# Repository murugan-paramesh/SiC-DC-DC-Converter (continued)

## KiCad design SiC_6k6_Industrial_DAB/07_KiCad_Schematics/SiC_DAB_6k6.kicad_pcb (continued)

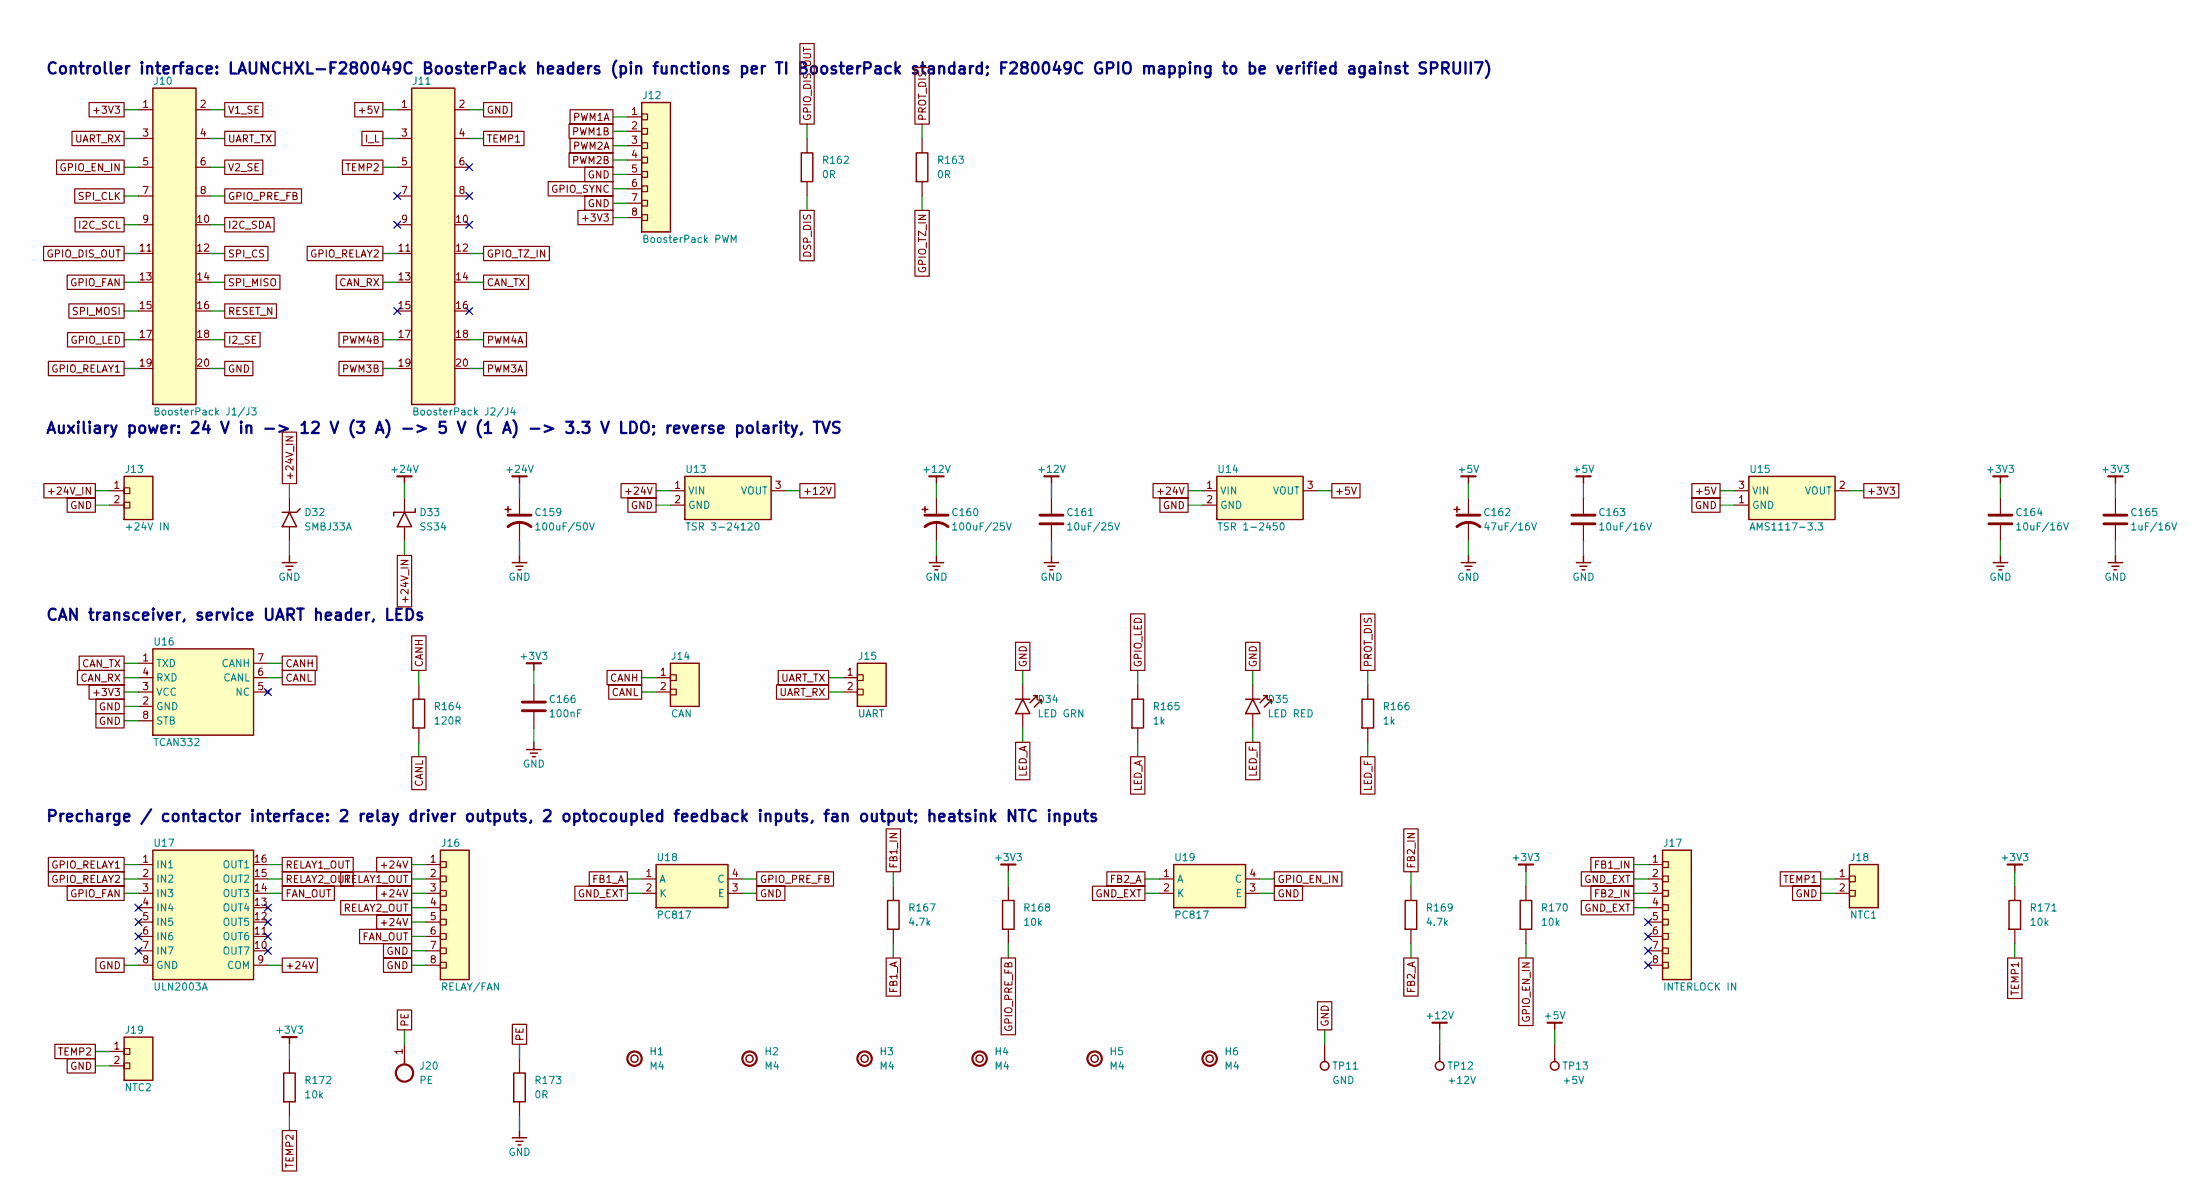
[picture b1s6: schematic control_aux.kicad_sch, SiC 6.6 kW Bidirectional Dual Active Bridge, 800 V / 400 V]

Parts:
C159: 100uF/50V; C_Radial_D8_P3.5
C160: 100uF/25V; C_Radial_D8_P3.5
C161: 10uF/25V; C_1206
C162: 47uF/16V; C_Radial_D8_P3.5
C163, C164: 10uF/16V; C_1206
C165: 1uF/16V; C_0603
C166: 100nF; C_0603
D32: SMBJ33A; D_SMA; MPN Littelfuse SMBJ33A
D33: SS34; D_SMA; MPN Vishay SS34
D34: LED GRN; LED_0805
D35: LED RED; LED_0805
H1, H2, H3, H4, H5, H6: M4; MountingHole_M4
J10: BoosterPack J1/J3; PinHeader_2x10_P2.54; MPN Samtec SSW-110-01-G-D class
J11: BoosterPack J2/J4; PinHeader_2x10_P2.54; MPN Samtec SSW-110-01-G-D class
J12: BoosterPack PWM; PinHeader_1x08_P2.54
J13: +24V IN; TerminalBlock_1x02_P5.08
J14: CAN; TerminalBlock_1x02_P5.08
J15: UART; PinHeader_1x02_P2.54
J16: RELAY/FAN; PinHeader_1x08_P2.54
J17: INTERLOCK IN; PinHeader_1x08_P2.54
J18: NTC1; PinHeader_1x02_P2.54
J19: NTC2; PinHeader_1x02_P2.54
J20: PE; Lug_M5
R162, R163: 0R; R_0603
R164: 120R; R_0603
R165, R166: 1k; R_0603
R167, R169: 4.7k; R_0805
R168, R170, R171, R172: 10k; R_0603
R173: 0R; R_1206
TP11: GND; TestPoint
TP12: +12V; TestPoint
TP13: +5V; TestPoint
U13: TSR 3-24120; SIP-3_TSR; MPN TRACO TSR 3-24120
U14: TSR 1-2450; SIP-3_TSR; MPN TRACO TSR 1-2450
U15: AMS1117-3.3; SOT-223; MPN AMS1117-3.3
U16: TCAN332; SOIC-8; MPN TI TCAN332D
U17: ULN2003A; SOIC-16; MPN TI ULN2003AD
U18, U19: PC817; DIP-4; MPN Sharp PC817

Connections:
+3V3: C164.1, C165.1, C166.1, J10.1, J12.8, R168.1, R170.1, R171.1, R172.1, U15.2 (VOUT), U16.3 (VCC); also elsewhere on the board
+5V: C162.1 (+), C163.1, J11.1, TP13.1, U14.3 (VOUT), U15.3 (VIN); also elsewhere on the board
+12V: C160.1 (+), C161.1, TP12.1, U13.3 (VOUT); also elsewhere on the board
+24V: C159.1 (+), D33.1 (K), J16.1, J16.3, J16.5, U13.1 (VIN), U14.1 (VIN), U17.9 (COM)
+24V_IN: D32.1 (K), D33.2 (A), J13.1
CANH: J14.1, R164.1, U16.7 (CANH)
CANL: J14.2, R164.2, U16.6 (CANL)
CAN_RX: J11.13, U16.4 (RXD)
CAN_TX: J11.14, U16.1 (TXD)
DSP_DIS: R162.2; also elsewhere on the board
FAN_OUT: J16.6, U17.14 (OUT3)
FB1_A: R167.2, U18.1 (A)
FB1_IN: J17.1, R167.1
FB2_A: R169.2, U19.1 (A)
FB2_IN: J17.3, R169.1
GND: C159.2 (-), C160.2 (-), C161.2, C162.2 (-), C163.2, C164.2, C165.2, C166.2, D32.2 (A), D34.1 (K), D35.1 (K), J10.20, J11.2, J12.5, J12.7, J13.2, J16.7, J16.8, J18.2, J19.2, R173.2, TP11.1, U13.2 (GND), U14.2 (GND), U15.1 (GND), U16.2 (GND), U16.8 (STB), U17.8 (GND), U18.3 (E), U19.3 (E); also elsewhere on the board
GND_EXT: J17.2, J17.4, U18.2 (K), U19.2 (K)
GPIO_DIS_OUT: J10.11, R162.1
GPIO_EN_IN: J10.5, R170.2, U19.4 (C)
GPIO_FAN: J10.13, U17.3 (IN3)
GPIO_LED: J10.17, R165.1
GPIO_PRE_FB: J10.8, R168.2, U18.4 (C)
GPIO_RELAY1: J10.19, U17.1 (IN1)
GPIO_RELAY2: J11.11, U17.2 (IN2)
GPIO_SYNC: J12.6
GPIO_TZ_IN: J11.12, R163.2
I2C_SCL: J10.9
I2C_SDA: J10.10
I2_SE: J10.18; also elsewhere on the board
I_L: J11.3; also elsewhere on the board
LED_A: D34.2 (A), R165.2
LED_F: D35.2 (A), R166.2
PE: J20.1, R173.1
PROT_DIS: R163.1, R166.1; also elsewhere on the board
PWM1A: J12.1; also elsewhere on the board
PWM1B: J12.2; also elsewhere on the board
PWM2A: J12.3; also elsewhere on the board
PWM2B: J12.4; also elsewhere on the board
PWM3A: J11.20; also elsewhere on the board
PWM3B: J11.19; also elsewhere on the board
PWM4A: J11.18; also elsewhere on the board
PWM4B: J11.17; also elsewhere on the board
RELAY1_OUT: J16.2, U17.16 (OUT1)
RELAY2_OUT: J16.4, U17.15 (OUT2)
RESET_N: J10.16
SPI_CLK: J10.7
SPI_CS: J10.12
SPI_MISO: J10.14
SPI_MOSI: J10.15
TEMP1: J11.4, J18.1, R171.2
TEMP2: J11.5, J19.1, R172.2
UART_RX: J10.3, J15.2
UART_TX: J10.4, J15.1
V1_SE: J10.2; also elsewhere on the board
V2_SE: J10.6; also elsewhere on the board

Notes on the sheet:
Controller interface: LAUNCHXL-F280049C BoosterPack headers (pin functions per TI BoosterPack standard; F280049C GPIO mapping to be verified against SPRUII7)
Auxiliary power: 24 V in -> 12 V (3 A) -> 5 V (1 A) -> 3.3 V LDO; reverse polarity, TVS
CAN transceiver, service UART header, LEDs
Precharge / contactor interface: 2 relay driver outputs, 2 optocoupled feedback inputs, fan output; heatsink NTC inputs

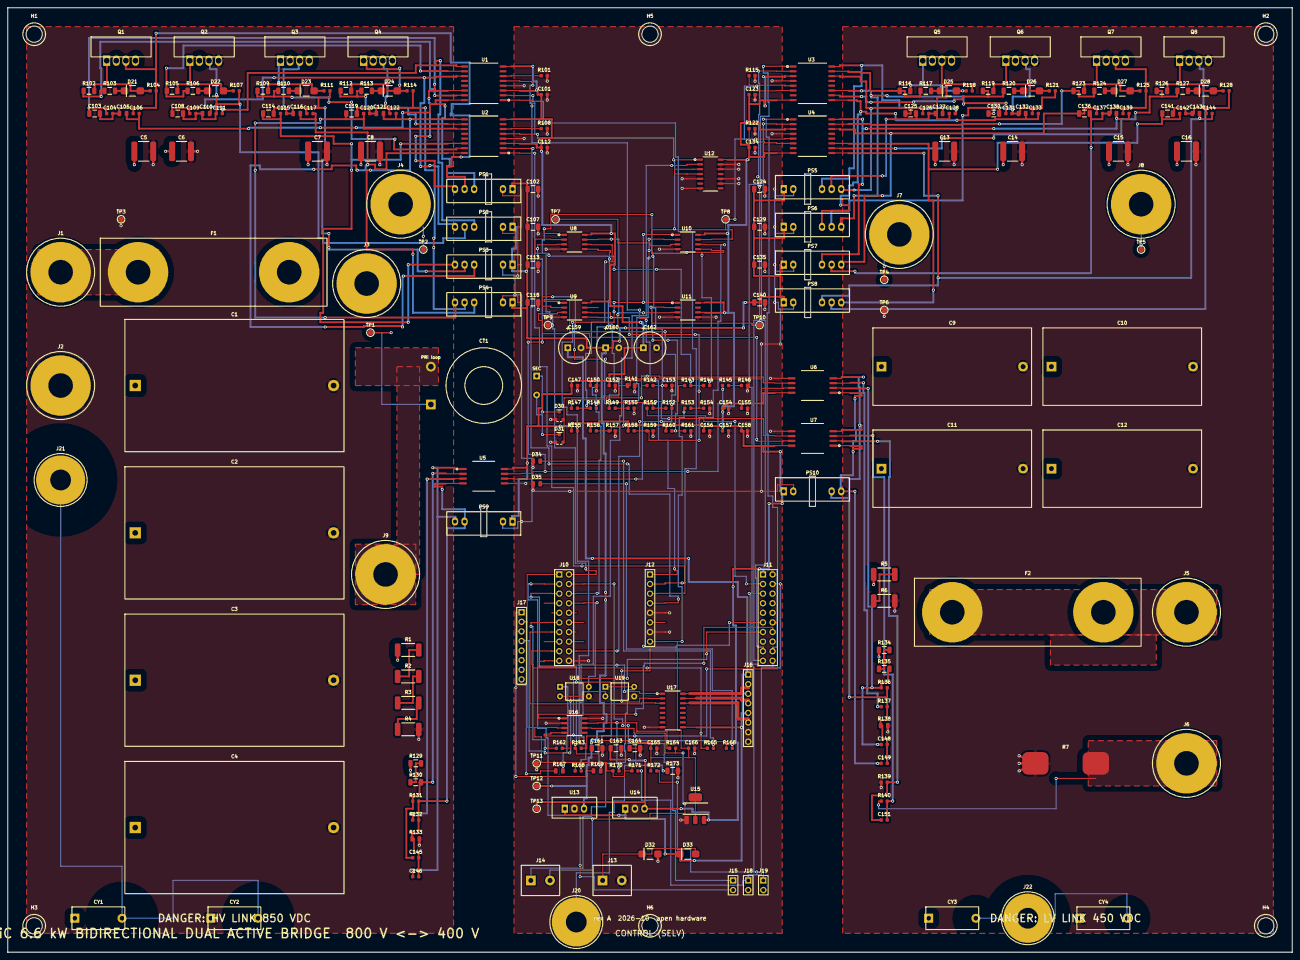
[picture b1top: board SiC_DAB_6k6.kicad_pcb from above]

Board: 6 copper layers, 340.0 x 250.0 mm, 261 parts (0 on the bottom side), 148 nets.

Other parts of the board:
J21: PE_HV; Lug_M5
J22: PE_LV; Lug_M5

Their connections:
PE_HV: J21.1; also elsewhere on the board
PE_LV: J22.1; also elsewhere on the board

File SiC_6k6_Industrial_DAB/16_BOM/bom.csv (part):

qty,refs,value,package,manufacturer,mpn,rating,datasheet,unit_cost,alternatives,procurement,description
4,"C1, C2, C3, C4",20uF/1100V,C_Film_P52.5,TDK,B32778J0206K (verify 1100 V variant),"film, 1100 V DC; used at 850 V (77 %)",https://www.tdk-electronics.tdk.com/,not verified,,PART SELECTION TO VERIFY,HV DC-link film capacitor
5,"C101, C112, C123, C134, C165",1uF/16V,C_0603,,,,,not verified,,PART SELECTION TO VERIFY,U1 VCCI decoupling
17,"C102, C103, C107, C108, C113, C114, C118, C119, C124, C125, C129, C130, C135, C136, C140, C141, C161",10uF/25V,C_1206,,,,,not verified,,PART SELECTION TO VERIFY,PS1 input capacitor
16,"C104, C106, C109, C111, C115, C117, C120, C122, C126, C128, C131, C133, C137, C139, C142, C144",1uF/50V,C_0603,,,,,not verified,,PART SELECTION TO VERIFY,Q1 +15 V HF
8,"C105, C110, C116, C121, C127, C132, C138, C143",4.7uF/25V,C_0805,,,,,not verified,,PART SELECTION TO VERIFY,Q1 -3 V bulk
4,"C13, C14, C15, C16",220nF/630V,C_2220,TDK,CGA9P4X7T2J224K (verify),X7T 630 V MLCC; used at 450 V (71 %),,not verified,,PART SELECTION TO VERIFY,"LV bridge HF decoupling, one pair per leg"
2,"C145, C148",1nF,C_0603,,,,,not verified,,PART SELECTION TO VERIFY,HV sense filter
11,"C146, C147, C149, C150, C152, C154, C155, C156, C157, C158, C166",100nF,C_0603,,,,,not verified,,PART SELECTION TO VERIFY,AMC1301 VDD1 decoupling
1,C151,10nF,C_0603,,,,,not verified,,PART SELECTION TO VERIFY,Shunt sense differential filter
1,C153,220pF,C_0603,,,,,not verified,,PART SELECTION TO VERIFY,I_L filter C0G
1,C159,100uF/50V,C_Radial_D8_P3.5,,,,,not verified,,PART SELECTION TO VERIFY,24 V bulk
1,C160,100uF/25V,C_Radial_D8_P3.5,,,,,not verified,,PART SELECTION TO VERIFY,12 V bulk
1,C162,47uF/16V,C_Radial_D8_P3.5,,,,,not verified,,PART SELECTION TO VERIFY,5 V bulk
2,"C163, C164",10uF/16V,C_1206,,,,,not verified,,PART SELECTION TO VERIFY,5 V HF
4,"C5, C6, C7, C8",100nF/1kV,C_2220,TDK,CGA9N4X7T2W104K (verify),X7T 1 kV MLCC; used at 850 V (85 %) - consider 2 kV part,,not verified,,PART SELECTION TO VERIFY,"HV bridge HF decoupling, one pair per leg"
4,"C9, C10, C11, C12",30uF/700V,C_Film_P37.5,TDK,B32778G7306K (verify),"film, 700 V DC; used at 450 V (64 %)",https://www.tdk-electronics.tdk.com/,not verified,,PART SELECTION TO VERIFY,LV DC-link film capacitor
1,CT1,CT 1:100,CT_Toroid_Straddle,Magnetics,ZW42908TC + 100T AWG32,,,not verified,,,Inductor current CT: one-turn insulated lead from J3 (SW_A) to the external inductor; secondary on the control side
4,"CY1, CY2, CY3, CY4",4.7nF Y1,C_Y1_P12.5,Vishay,VY1472M63Y5UQ63V0,"Y1 safety capacitor, 500 Vac",https://www.vishay.com/,not verified,,,Y1 capacitor HV+ to PE (first CM filter element)
8,"D21, D22, D23, D24, D25, D26, D27, D28",SS14,D_SMA,Vishay,SS14,,,not verified,,,Q1 turn-off steering diode
2,"D30, D31",BAV99,SOT-23,,,,,not verified,,PART SELECTION TO VERIFY,CT bridge rectifier half
1,D32,SMBJ33A,D_SMA,Littelfuse,SMBJ33A,,,not verified,,,24 V input TVS
1,D33,SS34,D_SMA,Vishay,SS34,,,not verified,,,Reverse-polarity series diode
1,D34,LED GRN,LED_0805,,,,,not verified,,PART SELECTION TO VERIFY,Status LED
1,D35,LED RED,LED_0805,,,,,not verified,,PART SELECTION TO VERIFY,Fault LED (PROT_DIS)
1,F1,16A/1000V,Fuse_Terminal_M6,Bussmann,FWP-16A14F class (verify),,,not verified,,PART SELECTION TO VERIFY,HV semiconductor fuse on M6 terminals
1,F2,32A/700V,Fuse_Terminal_M6,Bussmann,FWP-32A14F class (verify),,,not verified,,PART SELECTION TO VERIFY,LV semiconductor fuse on M6 terminals
1,J1,HV+,Stud_M6,,,,,not verified,,PART SELECTION TO VERIFY,HV port + (M6 stud); external semiconductor fuse 16 A/1000 V and precharge contactor in series
1,J10,BoosterPack J1/J3,PinHeader_2x10_P2.54,Samtec,SSW-110-01-G-D class,,,not verified,,PINOUT TO VERIFY ; PART SELECTION TO VERIFY,BoosterPack header 1 (pins 1-20)
1,J11,BoosterPack J2/J4,PinHeader_2x10_P2.54,Samtec,SSW-110-01-G-D class,,,not verified,,PINOUT TO VERIFY ; PART SELECTION TO VERIFY,"BoosterPack header 2 (pins 21-40); PWM1A/B, PWM2A/B on the third header J12"
1,J12,BoosterPack PWM,PinHeader_1x08_P2.54,,,,,not verified,,PINOUT TO VERIFY ; PART SELECTION TO VERIFY,"Additional PWM header (LaunchPad J5/J6 extension), to be mapped"
1,J13,+24V IN,TerminalBlock_1x02_P5.08,,,,,not verified,,PART SELECTION TO VERIFY,24 V auxiliary input
1,J14,CAN,TerminalBlock_1x02_P5.08,,,,,not verified,,PART SELECTION TO VERIFY,CAN bus terminal
1,J15,UART,PinHeader_1x02_P2.54,,,,,not verified,,PART SELECTION TO VERIFY,Service UART (3.3 V)
1,J16,RELAY/FAN,PinHeader_1x08_P2.54,,,,,not verified,,PART SELECTION TO VERIFY,"Contactor coil and fan outputs (24 V, 500 mA max each)"
1,J17,INTERLOCK IN,PinHeader_1x08_P2.54,,,,,not verified,,PART SELECTION TO VERIFY,"Isolated 24 V inputs: precharge feedback, external enable"
1,J18,NTC1,PinHeader_1x02_P2.54,,,,,not verified,,PART SELECTION TO VERIFY,HV heatsink NTC 10k
1,J19,NTC2,PinHeader_1x02_P2.54,,,,,not verified,,PART SELECTION TO VERIFY,LV heatsink NTC 10k
1,J2,HV-,Stud_M6,,,,,not verified,,PART SELECTION TO VERIFY,HV port -
1,J20,PE,Lug_M5,,,,,not verified,,PART SELECTION TO VERIFY,Protective earth stud (bonded to heatsinks and enclosure)
1,J21,PE_HV,Lug_M5,,,,,not verified,,PART SELECTION TO VERIFY,"PE lug of the HV region: Y-capacitor return, bonded to the HV heatsink / enclosure (the three PE lugs are joined through the chassis, not on the PCB, because no copper may cross the isolation barriers)"
1,J22,PE_LV,Lug_M5,,,,,not verified,,PART SELECTION TO VERIFY,"PE lug of the LV region: Y-capacitor return, bonded to the LV heatsink / enclosure"
1,J3,SW_A,Stud_M6,,,,,not verified,,PART SELECTION TO VERIFY,HV bridge output A -> external series inductor L1
1,J4,SW_B,Stud_M6,,,,,not verified,,PART SELECTION TO VERIFY,HV bridge output B -> transformer primary
1,J5,LV+,Stud_M6,,,,,not verified,,PART SELECTION TO VERIFY,LV port + (M6 stud); external fuse/contactor in series
1,J6,LV-,Stud_M6,,,,,not verified,,PART SELECTION TO VERIFY,LV port - (through the current shunt)
1,J7,SW_C,Stud_M6,,,,,not verified,,PART SELECTION TO VERIFY,LV bridge output C -> transformer secondary
1,J8,SW_D,Stud_M6,,,,,not verified,,PART SELECTION TO VERIFY,LV bridge output D -> transformer secondary
1,J9,L1 (via CT),Stud_M6,,,,,not verified,,PART SELECTION TO VERIFY,Stud for the inductor lead after the CT loop
8,"PS1, PS2, PS3, PS4, PS5, PS6, PS7, PS8",R12P21503D,SIP-7_IsoDCDC,RECOM,"R12P21503D (basic-class isolation; reinforced-rated module is an open item, see 15.1)","2 W, 5.2 kVDC isolation (basic class) - open item 15.1",https://recom-power.com/,not verified,,PINOUT TO VERIFY ; PART SELECTION TO VERIFY,Isolated gate bias Q1
1,PS10,ISO 5V/5V 1W SIP-7,SIP-7_IsoDCDC_1W,TBD,- as PS9,"1 W isolated 5 V module, SIP-7 outline, reinforced-rated part to be selected (open item 15.1)",,not verified,,PINOUT TO VERIFY,1 W isolated 5 V for the LV-side sensors
1,PS9,ISO 5V/5V 1W SIP-7,SIP-7_IsoDCDC_1W,TBD,"- 1 W 5 V->5 V isolated module, SIP-7 outline with >= 7.6 mm input/output pin gap, reinforced-rated (a 2.54 mm pitch SIP-4 such as R1SE cannot meet the 5.5 mm module creepage rule)","1 W isolated 5 V module, SIP-7 outline, reinforced-rated part to be selected (open item 15.1)",,not verified,,PINOUT TO VERIFY,1 W isolated 5 V for the HV-side sensor
4,"Q1, Q2, Q3, Q4",C3M0032120K,TO-247-4_Vertical,Wolfspeed,C3M0032120K,"1200 V, 32 mOhm, Tj 175 C; used at 850 V (71 %), Tj < 70 C calc.",https://www.wolfspeed.com/c3m0032120k/,not verified,,,"HV bridge SiC MOSFET 1200 V, high side leg A"
4,"Q5, Q6, Q7, Q8",C3M0016120K,TO-247-4_Vertical,Wolfspeed,C3M0016120K,"1200 V, 16 mOhm; used at 450 V (38 %)",https://www.wolfspeed.com/c3m0016120k/,not verified,,,"LV bridge SiC MOSFET 1200 V, high side leg C"
4,"R1, R2, R3, R4",680k/2W,R_2512,,,"2512, 2 W; 212 V per resistor (voltage rating 500 V)",,not verified,,PART SELECTION TO VERIFY,"HV bleeder chain 2.7 MOhm (4 x 680 k, 850 V / 4 = 212 V per resistor)"
4,"R101, R108, R115, R122",2.2k,R_0603,,,,,not verified,,PART SELECTION TO VERIFY,U1 interlock dead time ~22 ns
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
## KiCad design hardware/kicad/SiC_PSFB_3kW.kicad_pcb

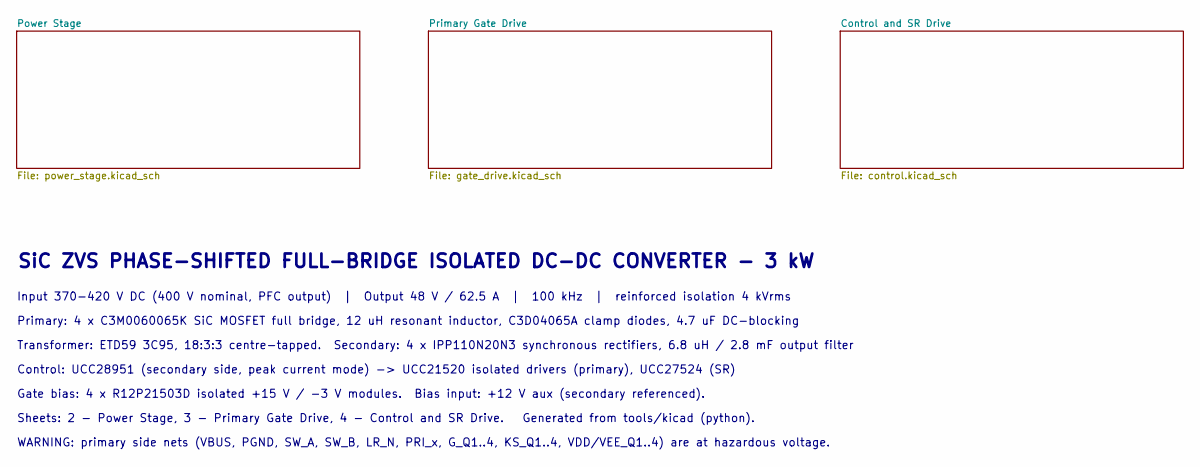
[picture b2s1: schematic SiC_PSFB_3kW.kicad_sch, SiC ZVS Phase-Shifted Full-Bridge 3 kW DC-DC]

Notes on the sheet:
SiC ZVS PHASE-SHIFTED FULL-BRIDGE ISOLATED DC-DC CONVERTER - 3 kW
Input 370-420 V DC (400 V nominal, PFC output) | Output 48 V / 62.5 A | 100 kHz | reinforced isolation 4 kVrms
Primary: 4 x C3M0060065K SiC MOSFET full bridge, 12 uH resonant inductor, C3D04065A clamp diodes, 4.7 uF DC-blocking
Transformer: ETD59 3C95, 18:3:3 centre-tapped. Secondary: 4 x IPP110N20N3 synchronous rectifiers, 6.8 uH / 2.8 mF output filter
Control: UCC28951 (secondary side, peak current mode) -> UCC21520 isolated drivers (primary), UCC27524 (SR)
Gate bias: 4 x R12P21503D isolated +15 V / -3 V modules. Bias input: +12 V aux (secondary referenced).
Sheets: 2 - Power Stage, 3 - Primary Gate Drive, 4 - Control and SR Drive. Generated from tools/kicad (python).
WARNING: primary side nets (VBUS, PGND, SW_A, SW_B, LR_N, PRI_x, G_Q1..4, KS_Q1..4, VDD/VEE_Q1..4) are at hazardous voltage.

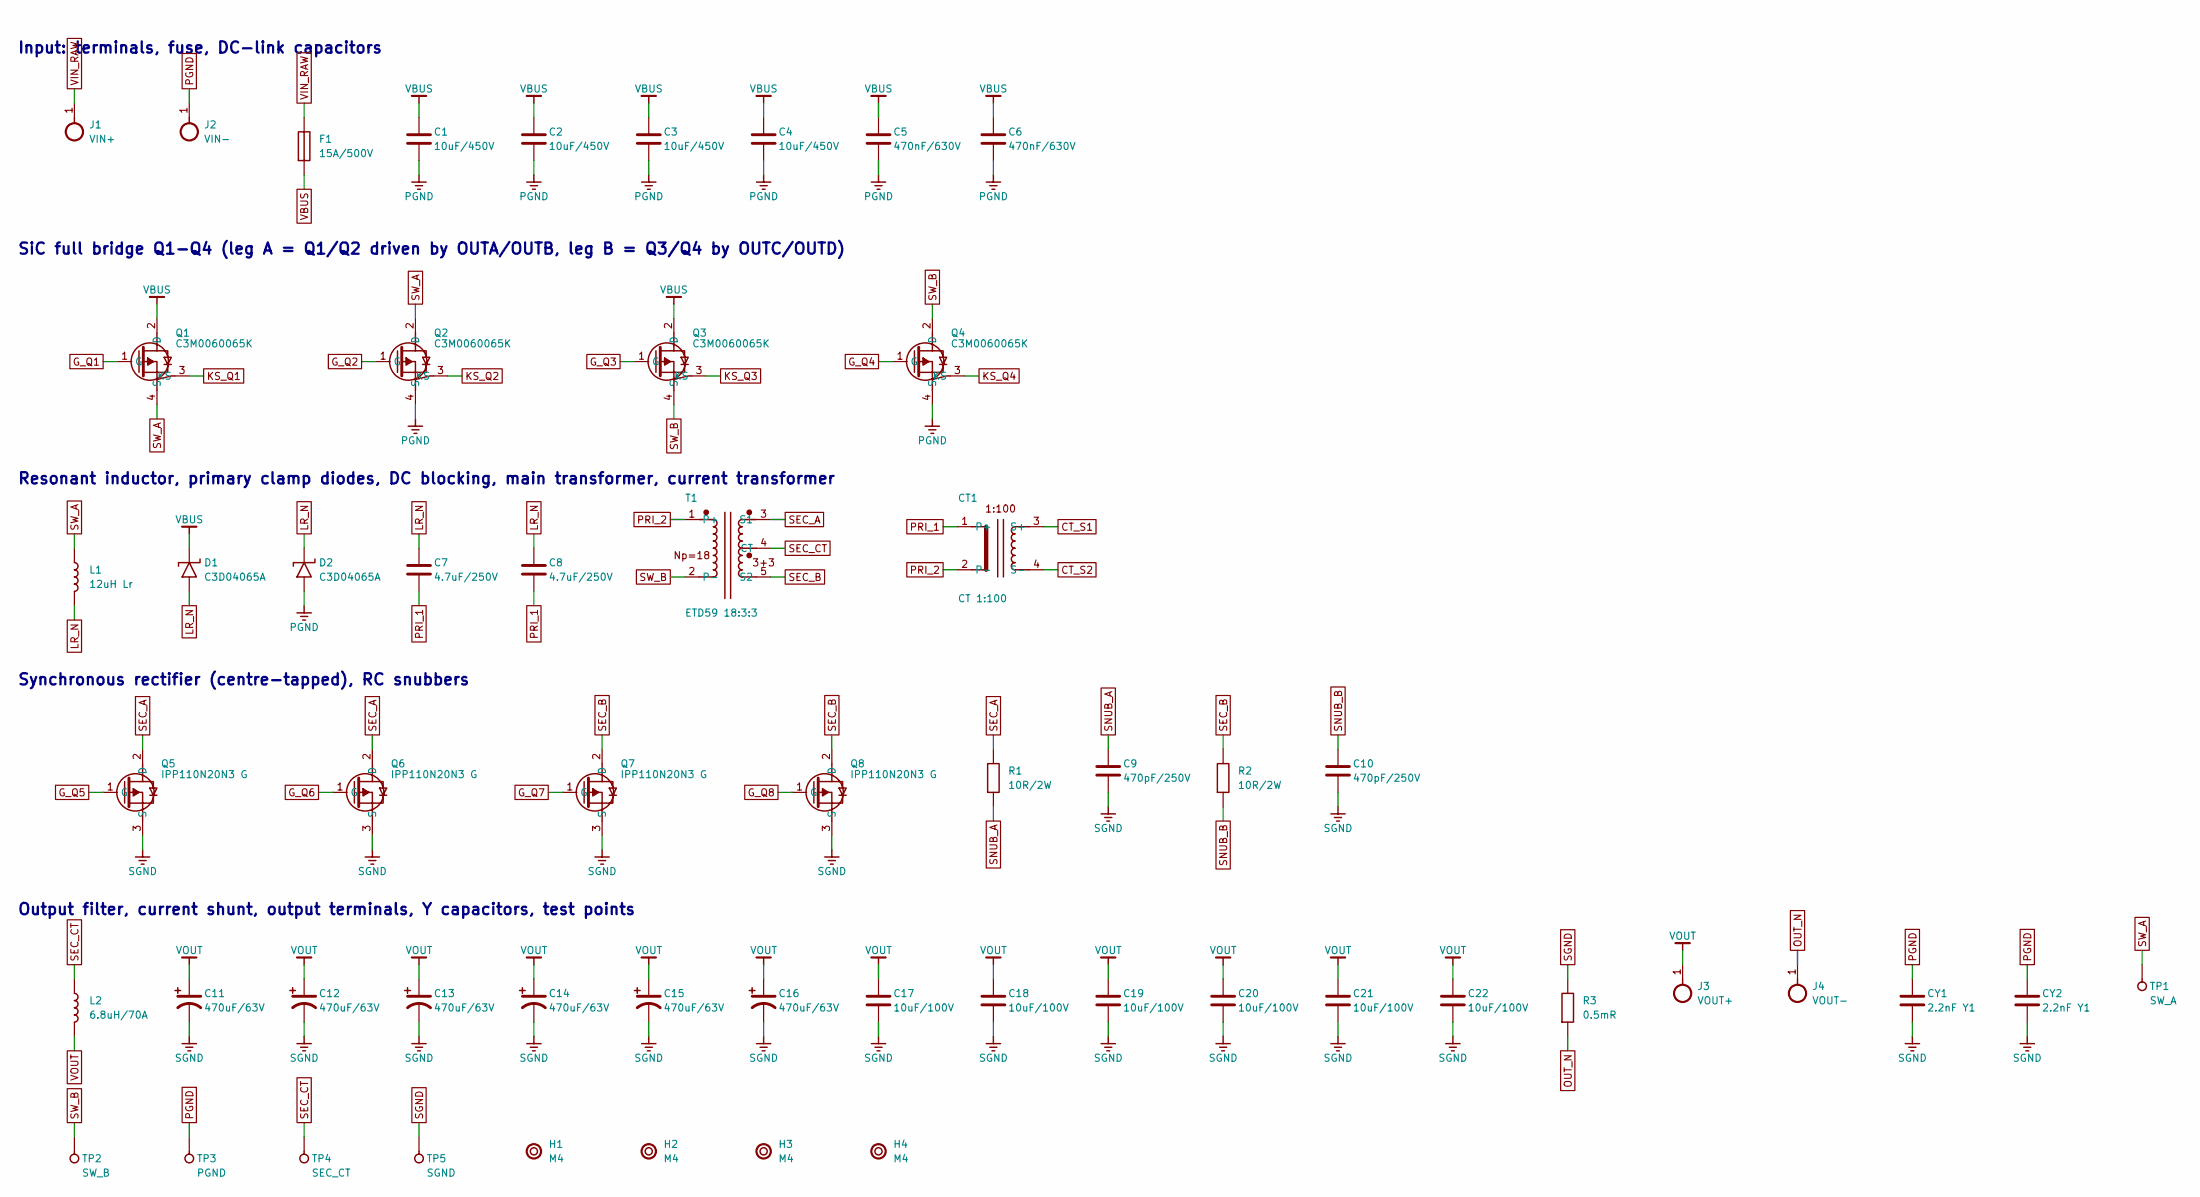
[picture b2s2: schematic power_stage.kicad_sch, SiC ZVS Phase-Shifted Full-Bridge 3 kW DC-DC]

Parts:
C1, C2, C3, C4: 10uF/450V; C_Film_P37.5; MPN TDK B32778G4106K
C5, C6: 470nF/630V; C_2220; MPN TDK CGA9P4X7T2J474K
C7, C8: 4.7uF/250V; C_Film_P22.5; MPN TDK B32674D3475K
C9, C10: 470pF/250V; C_1206
C11, C12, C13, C14, C15, C16: 470uF/63V; C_Radial_D16_P7.5; MPN Nichicon UHW1J471MHD
C17, C18, C19, C20, C21, C22: 10uF/100V; C_1210; MPN TDK CGA6P3X7S2A106K
CT1: CT 1:100; CT_Toroid_Straddle; MPN Magnetics ZW42908TC + 100T AWG32 (or Pu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
CY1, CY2: 2.2nF Y1; C_Y1_P12.5; MPN Vishay VY1222M63Y5UQ63V0
D1, D2: C3D04065A; TO-220-2_Vertical; MPN Wolfspeed C3D04065A
F1: 15A/500V; Fuse_6.3x32_Clips; MPN Littelfuse 0215015.MXP
H1, H2, H3, H4: M4; MountingHole_M4
J1: VIN+; Lug_M4
J2: VIN-; Lug_M4
J3: VOUT+; Lug_M5
J4: VOUT-; Lug_M5
L1: 12uH Lr; Inductor_ETD39_Lr; MPN custom ETD39/3C95 10T litz
L2: 6.8uH/70A; Inductor_Toroid_D52_Lo; MPN custom 2x Magnetics 77439-A7, 5T flat w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
Q1, Q2, Q3, Q4: C3M0060065K; TO-247-4_Vertical; MPN Wolfspeed C3M0060065K
Q5, Q6, Q7, Q8: IPP110N20N3 G; TO-220-3_Vertical; MPN Infineon IPP110N20N3 G
R1, R2: 10R/2W; R_2512
R3: 0.5mR; R_Shunt_8518; MPN Vishay WSBS8518L5000JK
T1: ETD59 18:3:3; Transformer_ETD59_PSFB; MPN custom, see docs/06
TP1: SW_A; TestPoint
TP2: SW_B; TestPoint
TP3: PGND; TestPoint
TP4: SEC_CT; TestPoint
TP5: SGND; TestPoint

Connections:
CT_S1: CT1.3 (S+); also elsewhere on the board
CT_S2: CT1.4 (S-); also elsewhere on the board
G_Q1: Q1.1 (G); also elsewhere on the board
G_Q2: Q2.1 (G); also elsewhere on the board
G_Q3: Q3.1 (G); also elsewhere on the board
G_Q4: Q4.1 (G); also elsewhere on the board
G_Q5: Q5.1 (G); also elsewhere on the board
G_Q6: Q6.1 (G); also elsewhere on the board
G_Q7: Q7.1 (G); also elsewhere on the board
G_Q8: Q8.1 (G); also elsewhere on the board
KS_Q1: Q1.3 (KS); also elsewhere on the board
KS_Q2: Q2.3 (KS); also elsewhere on the board
KS_Q3: Q3.3 (KS); also elsewhere on the board
KS_Q4: Q4.3 (KS); also elsewhere on the board
LR_N: C7.1, C8.1, D1.2 (A), D2.1 (K), L1.2
OUT_N: J4.1, R3.2; also elsewhere on the board
PGND: C1.2, C2.2, C3.2, C4.2, C5.2, C6.2, CY1.1, CY2.1, D2.2 (A), J2.1, Q2.4 (S), Q4.4 (S), TP3.1
PRI_1: C7.2, C8.2, CT1.1 (P+)
PRI_2: CT1.2 (P-), T1.1 (P+)
SEC_A: Q5.2 (D), Q6.2 (D), R1.1, T1.3 (S1)
SEC_B: Q7.2 (D), Q8.2 (D), R2.1, T1.5 (S2)
SEC_CT: L2.1, T1.4 (CT), TP4.1
SGND: C9.2, C10.2, C11.2 (-), C12.2 (-), C13.2 (-), C14.2 (-), C15.2 (-), C16.2 (-), C17.2, C18.2, C19.2, C20.2, C21.2, C22.2, CY1.2, CY2.2, Q5.3 (S), Q6.3 (S), Q7.3 (S), Q8.3 (S), R3.1, TP5.1; also elsewhere on the board
SNUB_A: C9.1, R1.2
SNUB_B: C10.1, R2.2
SW_A: L1.1, Q1.4 (S), Q2.2 (D), TP1.1
SW_B: Q3.4 (S), Q4.2 (D), T1.2 (P-), TP2.1
VBUS: C1.1, C2.1, C3.1, C4.1, C5.1, C6.1, D1.1 (K), F1.2, Q1.2 (D), Q3.2 (D)
VIN_RAW: F1.1, J1.1
VOUT: C11.1 (+), C12.1 (+), C13.1 (+), C14.1 (+), C15.1 (+), C16.1 (+), C17.1, C18.1, C19.1, C20.1, C21.1, C22.1, J3.1, L2.2; also elsewhere on the board

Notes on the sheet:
Input: terminals, fuse, DC-link capacitors
SiC full bridge Q1-Q4 (leg A = Q1/Q2 driven by OUTA/OUTB, leg B = Q3/Q4 by OUTC/OUTD)
Resonant inductor, primary clamp diodes, DC blocking, main transformer, current transformer
Synchronous rectifier (centre-tapped), RC snubbers
Output filter, current shunt, output terminals, Y capacitors, test points

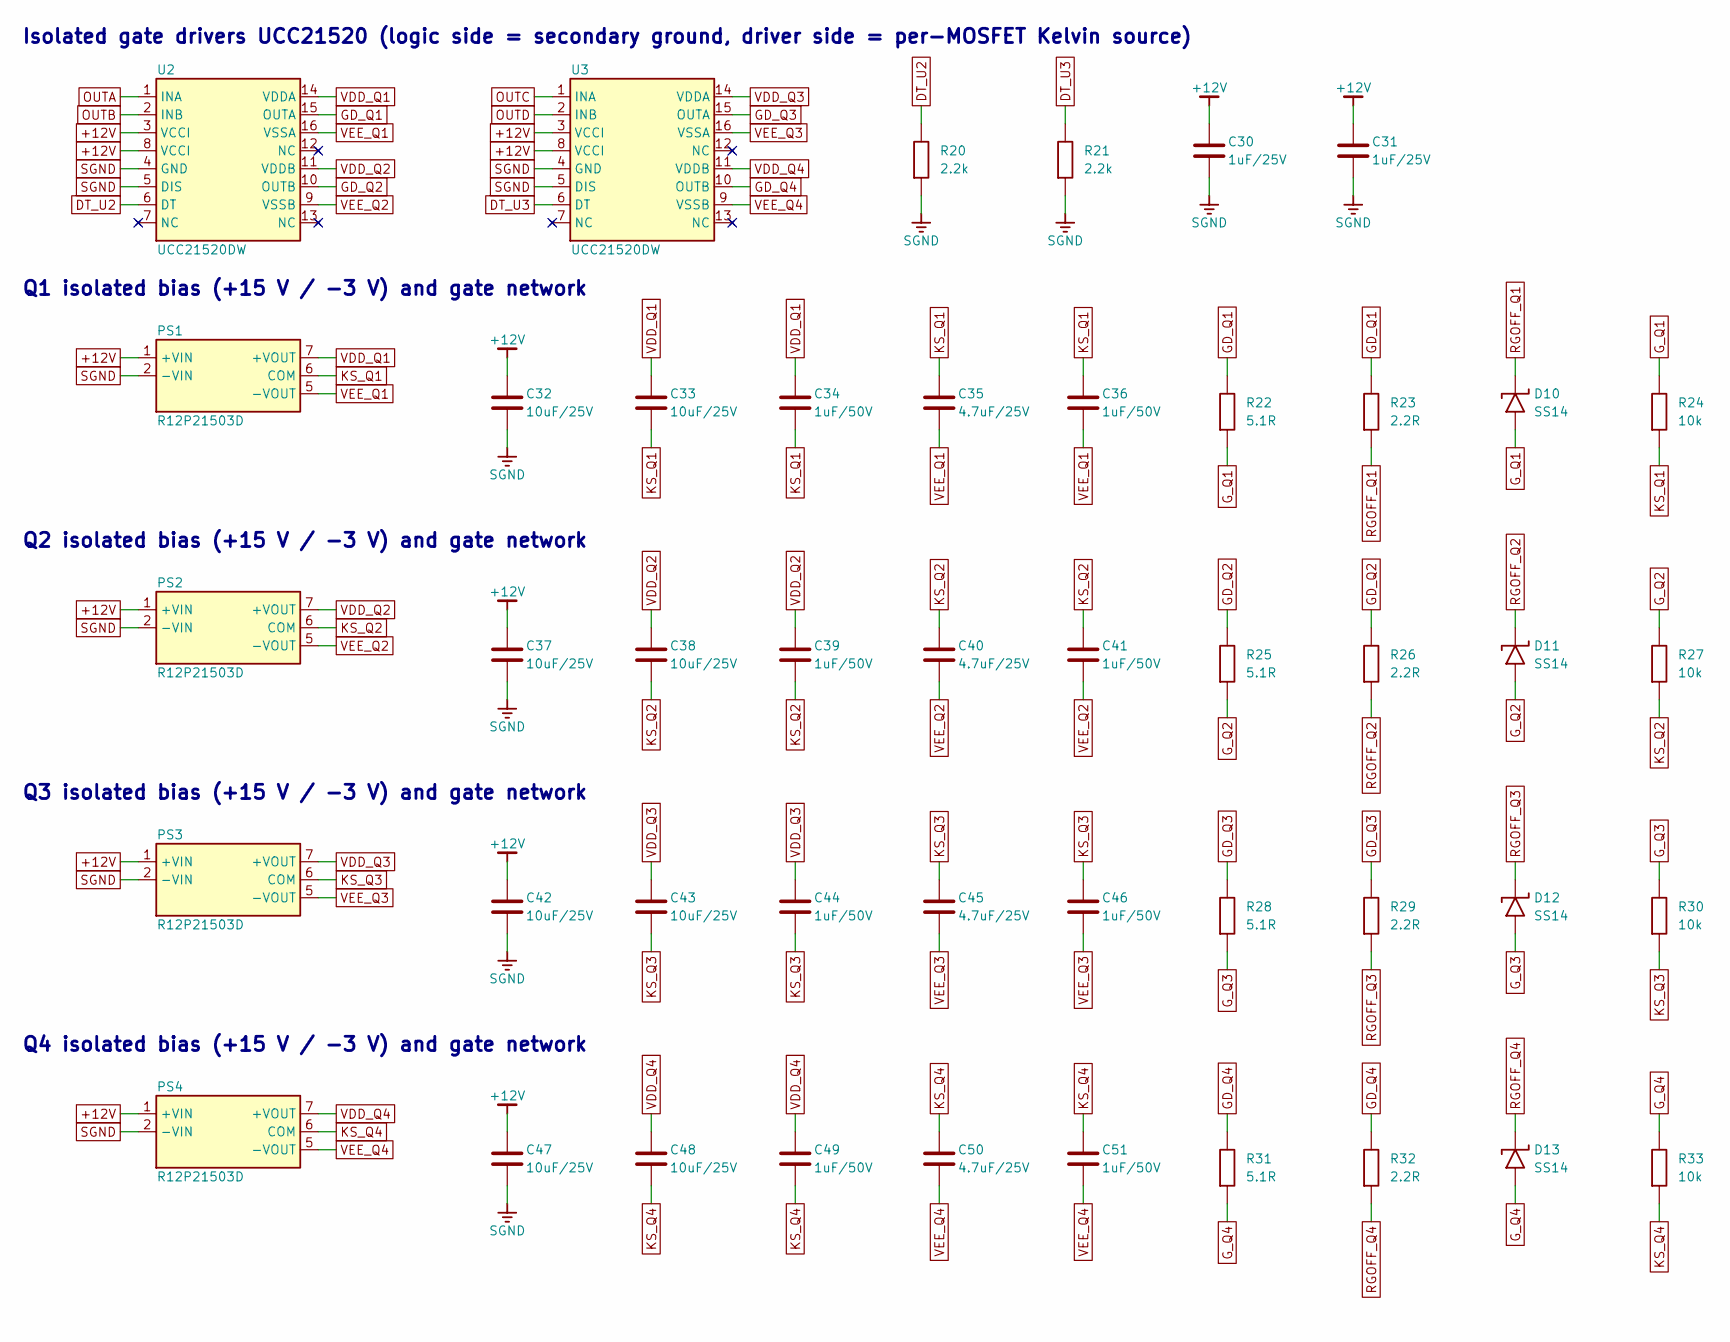
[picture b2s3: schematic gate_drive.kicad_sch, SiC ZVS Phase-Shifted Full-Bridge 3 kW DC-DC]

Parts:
C30, C31: 1uF/25V; C_0603
C32, C33, C37, C38, C42, C43, C47, C48: 10uF/25V; C_1206
C34, C36, C39, C41, C44, C46, C49, C51: 1uF/50V; C_0603
C35, C40, C45, C50: 4.7uF/25V; C_0805
D10, D11, D12, D13: SS14; D_SMA; MPN Vishay SS14
PS1, PS2, PS3, PS4: R12P21503D; SIP-7_IsoDCDC; MPN RECOM R12P21503D
R20, R21: 2.2k; R_0603
R22, R25, R28, R31: 5.1R; R_1206
R23, R26, R29, R32: 2.2R; R_1206
R24, R27, R30, R33: 10k; R_0603
U2, U3: UCC21520DW; SOIC-16W; MPN TI UCC21520DW

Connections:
+12V: C30.1, C31.1, C32.1, C37.1, C42.1, C47.1, PS1.1 (+VIN), PS2.1 (+VIN), PS3.1 (+VIN), PS4.1 (+VIN), U2.3 (VCCI), U2.8 (VCCI), U3.3 (VCCI), U3.8 (VCCI); also elsewhere on the board
DT_U2: R20.1, U2.6 (DT)
DT_U3: R21.1, U3.6 (DT)
GD_Q1: R22.1, R23.1, U2.15 (OUTA)
GD_Q2: R25.1, R26.1, U2.10 (OUTB)
GD_Q3: R28.1, R29.1, U3.15 (OUTA)
GD_Q4: R31.1, R32.1, U3.10 (OUTB)
G_Q1: D10.2 (A), R22.2, R24.1; also elsewhere on the board
G_Q2: D11.2 (A), R25.2, R27.1; also elsewhere on the board
G_Q3: D12.2 (A), R28.2, R30.1; also elsewhere on the board
G_Q4: D13.2 (A), R31.2, R33.1; also elsewhere on the board
KS_Q1: C33.2, C34.2, C35.1, C36.1, PS1.6 (COM), R24.2; also elsewhere on the board
KS_Q2: C38.2, C39.2, C40.1, C41.1, PS2.6 (COM), R27.2; also elsewhere on the board
KS_Q3: C43.2, C44.2, C45.1, C46.1, PS3.6 (COM), R30.2; also elsewhere on the board
KS_Q4: C48.2, C49.2, C50.1, C51.1, PS4.6 (COM), R33.2; also elsewhere on the board
OUTA: U2.1 (INA); also elsewhere on the board
OUTB: U2.2 (INB); also elsewhere on the board
OUTC: U3.1 (INA); also elsewhere on the board
OUTD: U3.2 (INB); also elsewhere on the board
RGOFF_Q1: D10.1 (K), R23.2
RGOFF_Q2: D11.1 (K), R26.2
RGOFF_Q3: D12.1 (K), R29.2
RGOFF_Q4: D13.1 (K), R32.2
SGND: C30.2, C31.2, C32.2, C37.2, C42.2, C47.2, PS1.2 (-VIN), PS2.2 (-VIN), PS3.2 (-VIN), PS4.2 (-VIN), R20.2, R21.2, U2.4 (GND), U2.5 (DIS), U3.4 (GND), U3.5 (DIS); also elsewhere on the board
VDD_Q1: C33.1, C34.1, PS1.7 (+VOUT), U2.14 (VDDA)
VDD_Q2: C38.1, C39.1, PS2.7 (+VOUT), U2.11 (VDDB)
VDD_Q3: C43.1, C44.1, PS3.7 (+VOUT), U3.14 (VDDA)
VDD_Q4: C48.1, C49.1, PS4.7 (+VOUT), U3.11 (VDDB)
VEE_Q1: C35.2, C36.2, PS1.5 (-VOUT), U2.16 (VSSA)
VEE_Q2: C40.2, C41.2, PS2.5 (-VOUT), U2.9 (VSSB)
VEE_Q3: C45.2, C46.2, PS3.5 (-VOUT), U3.16 (VSSA)
VEE_Q4: C50.2, C51.2, PS4.5 (-VOUT), U3.9 (VSSB)

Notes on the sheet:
Isolated gate drivers UCC21520 (logic side = secondary ground, driver side = per-MOSFET Kelvin source)
Q1 isolated bias (+15 V / -3 V) and gate network
Q2 isolated bias (+15 V / -3 V) and gate network
Q3 isolated bias (+15 V / -3 V) and gate network
Q4 isolated bias (+15 V / -3 V) and gate network
